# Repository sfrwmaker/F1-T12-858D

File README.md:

# F1-T12-858D
Soldering station for hakko t12 tips + 858D rework station

The project description is available here: https://www.hackster.io/sfrwmaker/stm32-based-soldering-and-rework-station-e3955b

REVISION HISTORY:

Nov 2019. First release created

Jan 2020. Second release created
  - Minor changes in the controller schematics
  - Now the Hot Air Gun reed switch controls working mode
  - The soldering iron can keep working while Hot Air Gun mode
  - Screen saver feature implemented
  
Jan 2020. Some updates of the second release
  - Minor changes in the controller schematics
  - Buzzer is always on issue fixed

Feb 11 2020. Error on Op-amp label on schematics fixed. LM328 - > LM358

Mar 23 2020. New firmware release, 2.02. See detailed description on the project page.
  - Updated Hot Air Gun cooling procedure
  - Debug mode added allowing monitoring of the internal parameters

Apr 17 2020. New firmware release, 2.03. See detailed description on the project page.
  - Two mode hardware switch supported: REED and TILT. Tilt switch algorithm updated. 
  - Fixed issue 'jammed on tip selection screen'. Now the main menu reacheble from tip selection mode by long press.
  - Ambient temperature and tilt switch readings now are available on debug screen.
  - Controller without soldering handle connected starts working in Hot Air Gun mode.

Apr 29 2020. New firmware release, 3.00. See detailed description on the project page.
  - Optional 220v safety relay added.
  - Rotary encoder acceleration deactivated.

May 12 2020. New firmware release, 3.01. See detailed description on the project page.
  - Standby mode issues fixed.
  - Temperature step feature added.
  
June 03 2020. New firmaware release, 3.02.
  - Hot Air GUN start issue fixed. The power is supplied to the Hot Gun in 1 second after it activated allowing enabling AC relay.
  - "About" menu item issue fixed. Now this menu is available.
  - Tilt switch procedures reviewed and updated.
  - The standby mode separated from main working mode and implemented as a new one.
  - Screen saver timeout now is a single entity. It is no longer depended on mode switching. To return to the normal screen mode, touch the encoder.
  - Software automatic power off procedure reviewed and updated. The controller can power off the iron in case of no tilt switch available.
  - Accelerated mode of rotary encoder implemented in setting low power temperature procedure in the main menu.
  
  Jan 03 2021. New firmware release, 4.00.
  - Display initialization method chhanged. Now the rotation parameter is inside the contstuctor in display.cpp.
  - Added support for 'Guarantee cool gun' feature. New feature requires the hardware to be updated.
    With new hardware schematics the controller guarantees the Hot Air Gun cooled before shutdown.
    You can put Hot Air Gun to the base then switch off the main power switch and leave your working place.
    The controller will switch-off the Hot Air Gun, waits till the Hot Air gun cooled and power-off itself.
    The new firmware release suports old hardware also. Of course, new 'guarantee cool gun feature' will not be available on old hardware.
    
  Jan 30 2021. New hardware and firmware release, 4.01. The schematics with relay has been simplified.
  - Support for 'Guarantee cool gun' feature changed. New feature requires the hardware to be updated. See stm32_T12+858D_v4.sch file in the eagle directory.
  
  Feb 01 2021. Release 4.02.
  - Fixed controller hangs after Hot Air Gun cooled issue.
  
  Apr 28 2021. Release 4.03.
  - Debug information about AC zero events added to the debug mode
  
  May 25 2021. Release 4.04.
  - New feature added. Now it is possible to manage soldering iron while in hot air gun mode. If the "keep iron" option is enabled in main menu, long-press the encoder toggles the soldering iron.
 
  May 30 2021. Release 4.05.
  - Automatic startup mode implemented. The soldering iron would power-up when the power applied to the controller if mode activated.
  - Boost mode updated. Now boost duration time can be increment by 20 seconds upto 320 seconds. Boost mode temperature now more stable.

  Jun 02 2021. Release 4.06
  - No "about" item menu bug fixed
  
  Sep 21 2021. Release 4.07
  - Support for system clock checking procedure added. The controller checks its clock speed at startup. In case the ckock is lower than 72 MHz, the error message will be displayed. To return to the working mode long press the encoder.
  
  Sep 22 2021. Revert to release 4.06
  - The controller speed inialized correctly alwas, the speed test is not necessary.
  - Some followers reported the new firmware does not work.
  - Restore old source files, rebuild the project. Perhaps, the issue is about the flash limit of the stm32 microcontroller.
 
 Apr 01 2022. Release 4.07
 - Rotaruy encoder manager improved
 - New PID parameters for the Hot Air Gun caliration procedure applied
 - New TIP, T12-D32 added to the tip list

 Nov 07 2023. Release 4.08
 - The CubeMX file and project are mirgated to STM32CubeIDE.
 - Implemented new PID algorithm, trying to prevent overheating the soldering iron during heating up.
 - Faster heat-up procedure of soldering iron.
 - New manage procedure for Hot Air Gun imported from my recent project of soldering station with JBC tips.

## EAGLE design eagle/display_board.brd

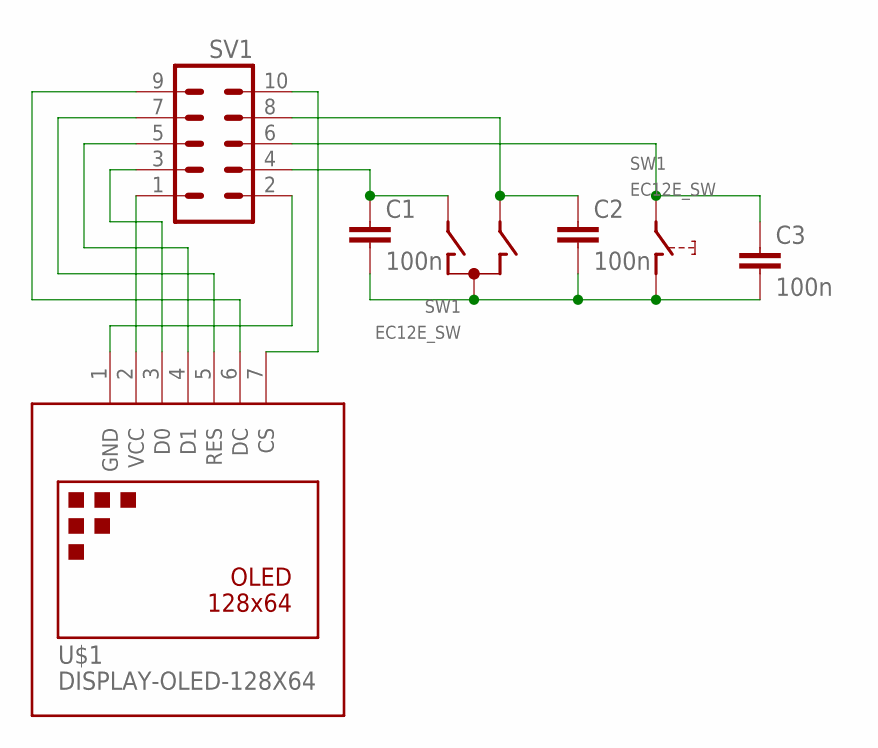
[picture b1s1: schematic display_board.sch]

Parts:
C1, C2, C3: 100n; C1206
SV1: MA05-2
SW1: EC12E_SW; ALPS_EC12E_SW
U$1: DISPLAY-OLED-128X64

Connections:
unnamed: SV1.1, U$1.2 (VCC)
unnamed: SV1.3, U$1.3 (D0)
unnamed: SV1.5, U$1.4 (D1)
unnamed: SV1.7, U$1.5 (RES)
unnamed: SV1.9, U$1.6 (DC)
unnamed: SV1.2, U$1.1 (GND)
unnamed: C1.1, SV1.4, SW1.A
unnamed: C1.2, C2.2, C3.2, SW1.C, SW1.D (1)
unnamed: C2.1, SV1.8, SW1.B
unnamed: C3.1, SV1.6, SW1.E (2)
unnamed: SV1.10, U$1.7 (CS)

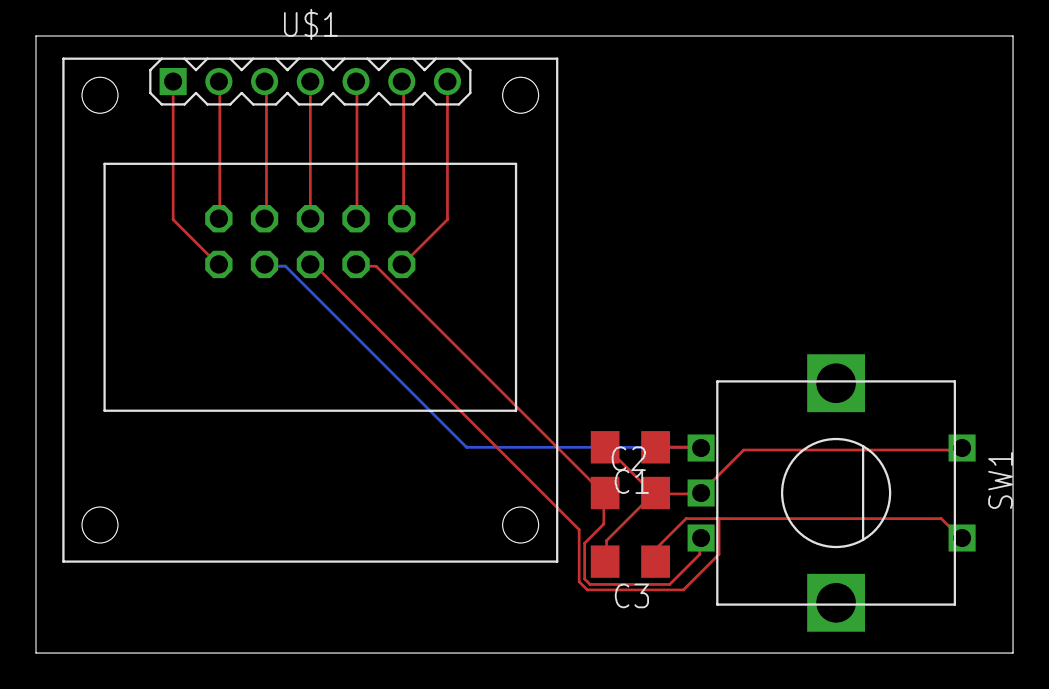
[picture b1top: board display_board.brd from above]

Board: 2 copper layers, 54.3 x 34.3 mm, 6 parts (1 on the bottom side), 11 nets.

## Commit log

2019-10-31 Create 1

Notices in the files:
parts and their libraries:
diy-modules: Released under the Creative Commons Attribution 4.0 International License: http://creativecommons.org/licenses/by/4.0
